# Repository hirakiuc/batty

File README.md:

# Batty Keyboard

The batty keyboard is a split keyboard which based on the [foostan/crkbd](https://github.com/foostan/crkbd).

## Layout

batty-classic has new two keys to each side from crkbd-classic.

## Firmware

This keyboard use qmk_firmare.
But not merged to [qmk/qmk_firmware](https://github.com/qmk/qmk_firmware), yet.

The batty firmware is under development on https://github.com/hirakiuc/qmk_firmware/tree/master/keyboards/batty

(Yes, The README of firmware is same with crkbd yet...)

# Copyrights

- batty logo
  - Original design created by [イラストK](https://illustk.com/3295/)

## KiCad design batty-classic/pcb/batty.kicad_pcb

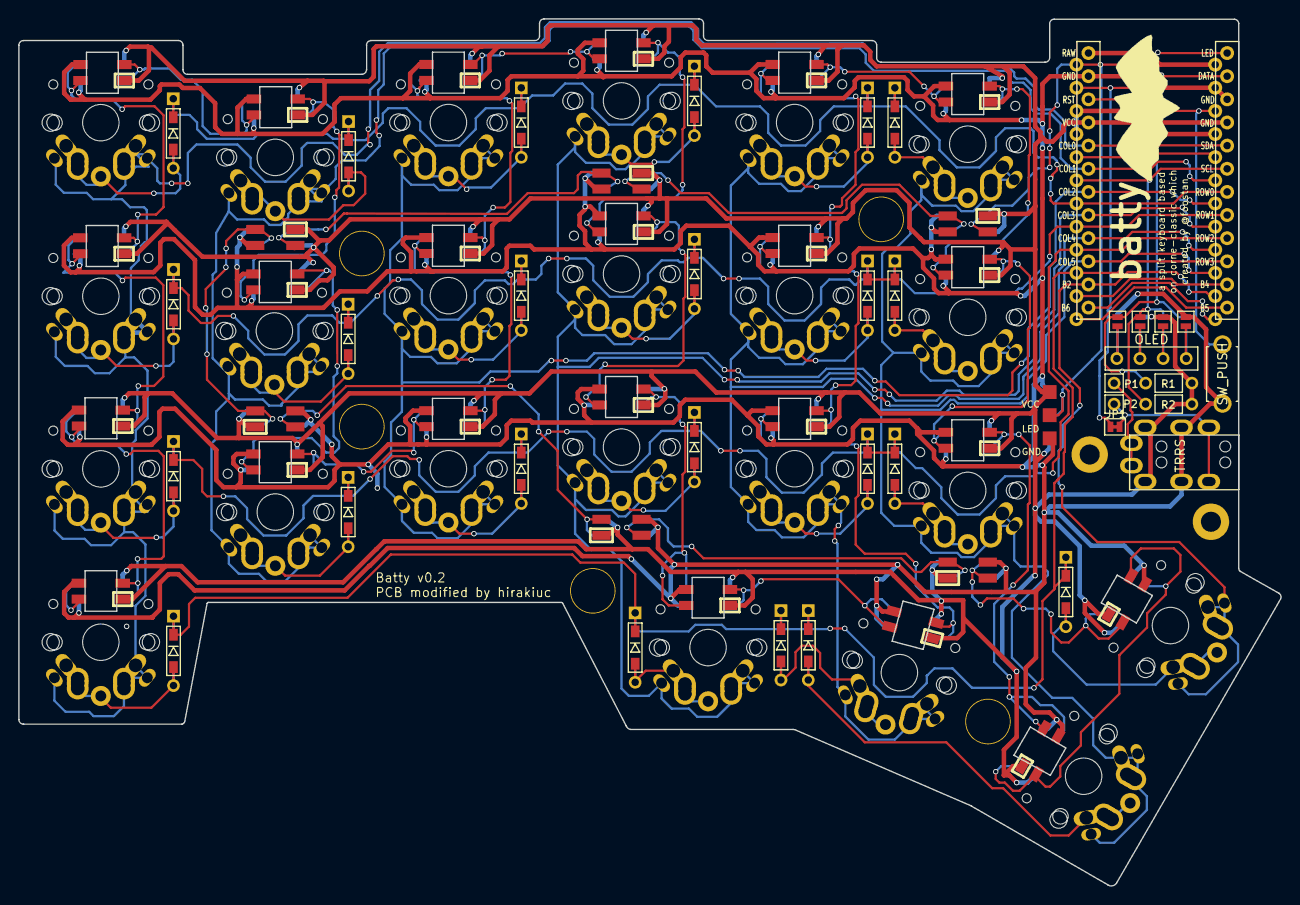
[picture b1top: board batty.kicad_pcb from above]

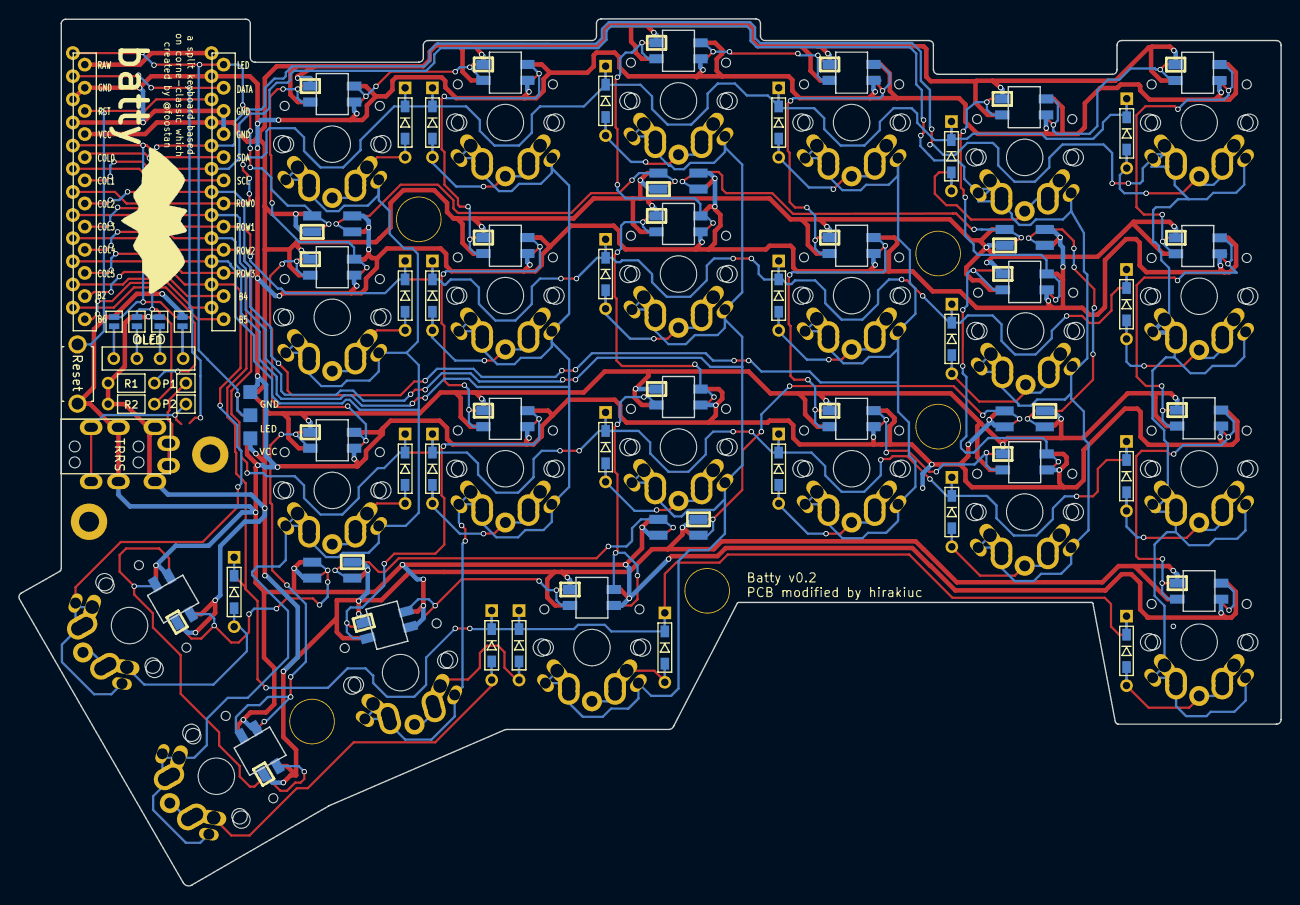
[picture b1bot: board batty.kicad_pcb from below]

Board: 2 copper layers, 138.5 x 95.2 mm, 93 parts (4 on the bottom side), 75 nets.

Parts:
D1, D2, D3, D4, D5, D6, D7, D8, D9, D10, D11, D12, D13, D14, D15, D16, D17, D18, D19, D20, D21, D22, D23: D; D3_TH_SMD
J1: MJ-4PP-9
J2: OLED
J3: LED; StripLED_rev
JP1: JP
JP2, JP3, JP4, JP5, JP6, JP7, JP8, JP9: Jumper
L1, L2, L3, L4, L5, L6: SK6812MINI; SK6812MINI_underglow_rev
L7, L8, L9, L10, L11, L12, L13, L14, L15, L16, L17, L18, L19, L20, L21, L22, L23, L24, L25, L26, L27, L28, L29: SK6812MINI; SK6812MINI_rev
P1, P2: i2c-pin; 1pin_conn
R1, R2: R
RSW1: SW_PUSH; ResetSW
SW1, SW2, SW3, SW4, SW5, SW6, SW7, SW8, SW9, SW10, SW11, SW12, SW13, SW14, SW15, SW16, SW17, SW18, SW19, SW20, SW21, SW22, SW23: SW_PUSH; MX_ALPS_PG1350_noLed
U1: ProMicro; ProMicro_v2

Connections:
GND: J1.C, J3.1, JP2.1, JP9.1, L1.2, L2.2, L3.2, L4.2, L5.2, L6.2, L7.2, L8.2, L9.2, L10.2, L11.2, L12.2, L13.2, L14.2, L15.2, L16.2, L17.2, L18.2, L19.2, L20.2, L21.2, L22.2, L23.2, L24.2, L25.2, L26.2, L27.2, L28.2, L29.2, RSW1.2, U1.3, U1.4, U1.23
LED: J3.2, L3.3, U1.1
unnamed: D1.2, SW1.2
unnamed: D2.2, SW2.2
unnamed: D3.2, SW3.2
unnamed: D4.2, SW4.2
unnamed: D5.2, SW5.2
unnamed: D6.2, SW6.2
unnamed: D7.2, SW7.2
unnamed: D8.2, SW8.2
unnamed: D9.2, SW9.2
unnamed: D10.2, SW10.2
unnamed: D11.2, SW11.2
unnamed: D12.2, SW12.2
unnamed: D13.2, SW13.2
unnamed: D14.2, SW14.2
unnamed: D15.2, SW15.2
unnamed: D16.2, SW16.2
unnamed: D17.2, SW17.2
unnamed: D18.2, SW18.2
unnamed: D19.2, SW19.2
unnamed: D20.2, SW20.2
unnamed: D21.2, SW21.2
unnamed: D22.2, SW22.2
unnamed: D23.2, SW23.2
unnamed: J1.A, P1.1
unnamed: J1.B, JP1.2, P2.1
unnamed: J2.1, JP5.2, JP9.2
unnamed: J2.2, JP4.2, JP8.2
unnamed: J2.3, JP3.2, JP7.2
unnamed: J2.4, JP2.2, JP6.2
unnamed: L1.1, L4.3
unnamed: L1.3, L2.1
unnamed: L2.3, L3.1
unnamed: L4.1, L5.3
unnamed: L5.1, L6.3
unnamed: L7.3, L8.1
unnamed: L9.3, L10.1
unnamed: L10.3, L16.1
unnamed: L11.1, L17.3
unnamed: L11.3, L12.1
unnamed: L12.3, L18.1
unnamed: L13.1, L19.3
unnamed: L7.1, L13.3
unnamed: L8.3, L14.1
unnamed: L14.3, L20.1
unnamed: L15.1, L21.3
unnamed: L9.1, L15.3
unnamed: L16.3, L22.1
unnamed: L17.1, L23.3
unnamed: L18.3, L24.1
unnamed: L19.1, L28.3
unnamed: L20.3, L21.1
unnamed: L22.3, L25.1
unnamed: L23.1, L26.3
unnamed: L24.3, L27.1
unnamed: L25.3, L26.1
unnamed: L27.3, L29.1
unnamed: L6.1, L29.3
SCL: JP4.1, JP7.1, R2.2, U1.6
SDA: JP5.1, JP6.1, R1.2, U1.5
VCC: J1.D, J3.3, JP3.1, JP8.1, L1.4, L2.4, L3.4, L4.4, L5.4, L6.4, L7.4, L8.4, L9.4, L10.4, L11.4, L12.4, L13.4, L14.4, L15.4, L16.4, L17.4, L18.4, L19.4, L20.4, L21.4, L22.4, L23.4, L24.4, L25.4, L26.4, L27.4, L28.4, L29.4, R1.1, R2.1, U1.21
col0: SW1.1, SW7.1, SW13.1, SW22.1, U1.20
col1: SW2.1, SW8.1, SW14.1, U1.19
col2: SW3.1, SW9.1, SW15.1, U1.18
col3: SW4.1, SW10.1, SW16.1, SW19.1, U1.17
col4: SW5.1, SW11.1, SW17.1, SW20.1, U1.16
col5: SW6.1, SW12.1, SW18.1, SW21.1, U1.15
col6: SW23.1, U1.14
data: JP1.1, U1.2
reset: RSW1.1, U1.22
row0: D1.1, D2.1, D3.1, D4.1, D5.1, D6.1, U1.7
row1: D7.1, D8.1, D9.1, D10.1, D11.1, D12.1, U1.8
row2: D13.1, D14.1, D15.1, D16.1, D17.1, D18.1, U1.9
row3: D19.1, D20.1, D21.1, D22.1, D23.1, U1.10

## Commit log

2018-11-18 Initial import
2018-11-19 fix release task
2018-11-19 add missing hole, update crkbd logo position.
2019-02-09 add batty-classic
2019-02-10 add images
2019-02-10 reduce image sizes
2019-02-10 resize logo image
2019-02-10 Add layout image and copyrights section.
2019-02-11 Add black logo
2019-02-12 fix line feed.
2019-02-15 add batty-classic/doc
2019-02-15 move batty-classic README.md
2019-02-16 Rename pbc to pcb...
2019-02-21 Add images to README
2023-02-27 Add batty-plate for yushakobo
